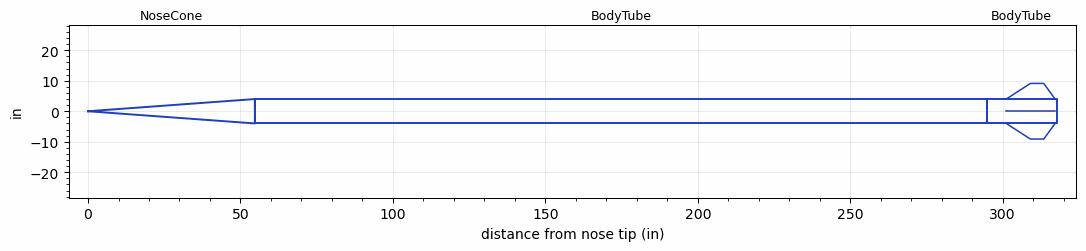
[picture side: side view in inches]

<RASAeroDocument>
 <FileVersion>2</FileVersion>
 <RocketDesign>
  <NoseCone>
   <Length>54.7243</Length>
   <Diameter>8</Diameter>
   <Shape>Conical</Shape>
   <Location>0</Location>
  </NoseCone>
  <BodyTube>
   <Length>239.9995</Length>
   <Diameter>8</Diameter>
   <Location>54.7243</Location>
  </BodyTube>
  <BodyTube>
   <Length>23</Length>
   <Diameter>8</Diameter>
   <Location>294.7238</Location>
   <Fin>
    <Count>4</Count>
    <Chord>16.0236</Chord>
    <Span>5.1181</Span>
    <SweepDistance>7.9134</SweepDistance>
    <TipChord>4.3975</TipChord>
    <Thickness>0.25</Thickness>
    <Location>16.5748</Location>
    <AirfoilSection>Square</AirfoilSection>
   </Fin>
  </BodyTube>
  <Surface>Rough Camouflage Paint</Surface>
  <CD>0</CD>
  <ModifiedBarrowman>False</ModifiedBarrowman>
  <Turbulence>False</Turbulence>
  <UseBooster1>False</UseBooster1>
  <UseBooster2>False</UseBooster2>
  <Comments>Testing for stability --&gt; upthrust sim</Comments>
 </RocketDesign>
 <LaunchSite>
  <Altitude>0</Altitude>
  <Pressure>29.9214</Pressure>
  <RodAngle>0</RodAngle>
  <RodLength>3.2808</RodLength>
  <Temperature>59</Temperature>
  <WindSpeed>4.4739</WindSpeed>
 </LaunchSite>
 <Recovery>
  <Altitude1>0</Altitude1>
  <Altitude2>0</Altitude2>
  <DeviceType1>None</DeviceType1>
  <DeviceType2>None</DeviceType2>
  <Event1>False</Event1>
  <Event2>False</Event2>
  <Size1>0</Size1>
  <Size2>0</Size2>
  <EventType1>None</EventType1>
  <EventType2>None</EventType2>
  <CD1>0</CD1>
  <CD2>0</CD2>
 </Recovery>
 <SimulationList>
  <Simulation>
   <SustainerLaunchWt>137.1875</SustainerLaunchWt>
   <SustainerCG>184.9301</SustainerCG>
   <SustainerIgnitionDelay>0</SustainerIgnitionDelay>
   <Booster1SeparationDelay>0</Booster1SeparationDelay>
   <Booster1IgnitionDelay>0</Booster1IgnitionDelay>
   <IncludeBooster1>False</IncludeBooster1>
   <Booster2Delay>0</Booster2Delay>
   <IncludeBooster2>False</IncludeBooster2>
  </Simulation>
 </SimulationList>
</RASAeroDocument>
